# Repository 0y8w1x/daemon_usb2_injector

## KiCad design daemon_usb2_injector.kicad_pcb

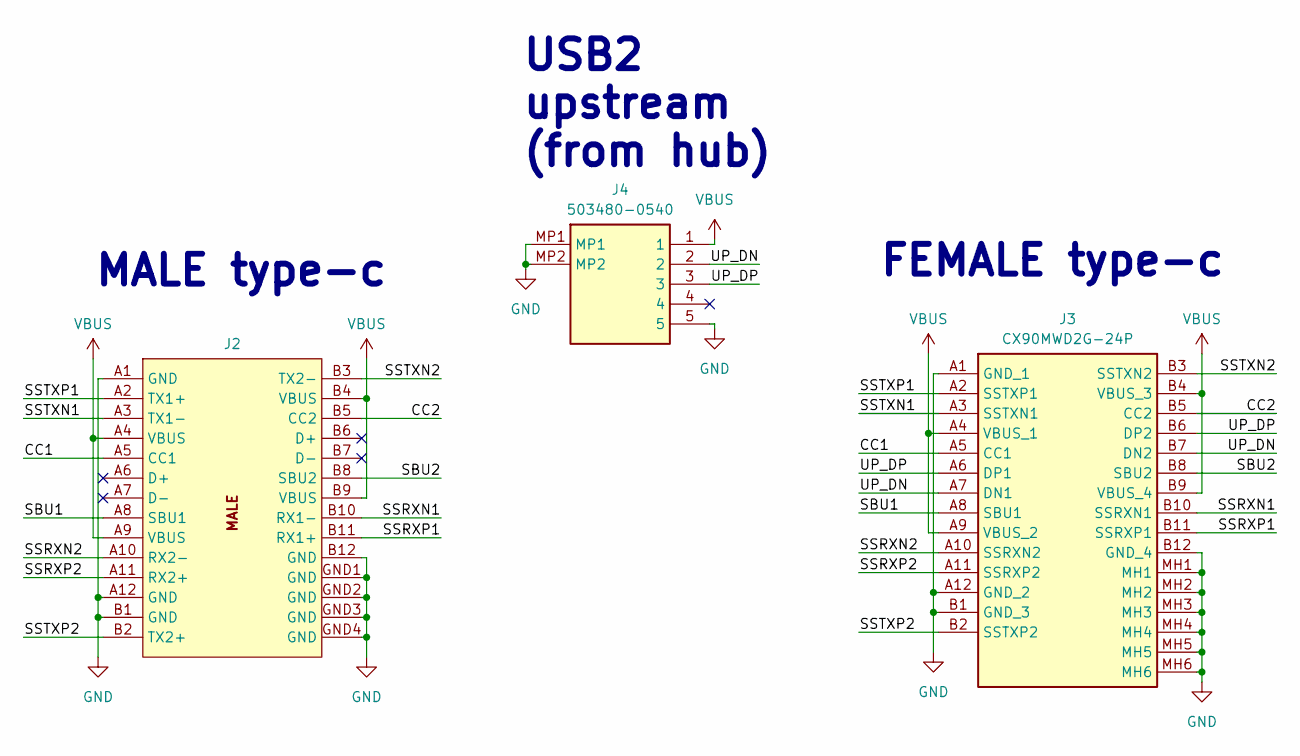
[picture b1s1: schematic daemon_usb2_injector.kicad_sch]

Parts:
J2: CX60-24S-UNIT
J3: CX90MWD2G-24P
J4: 503480-0540; 5034800540; Manufacturer_Part_Number 503480-0540; Mouser Part Number 538-503480-0540

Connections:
/CC1: J2.A5 (CC1), J3.A5 (CC1)
/CC2: J2.B5 (CC2), J3.B5 (CC2)
/SBU1: J2.A8 (SBU1), J3.A8 (SBU1)
/SBU2: J2.B8 (SBU2), J3.B8 (SBU2)
/SSRXN1: J2.B10 (RX1-), J3.B10 (SSRXN1)
/SSRXN2: J2.A10 (RX2-), J3.A10 (SSRXN2)
/SSRXP1: J2.B11 (RX1+), J3.B11 (SSRXP1)
/SSRXP2: J2.A11 (RX2+), J3.A11 (SSRXP2)
/SSTXN1: J2.A3 (TX1-), J3.A3 (SSTXN1)
/SSTXN2: J2.B3 (TX2-), J3.B3 (SSTXN2)
/SSTXP1: J2.A2 (TX1+), J3.A2 (SSTXP1)
/SSTXP2: J2.B2 (TX2+), J3.B2 (SSTXP2)
/UP_DN: J3.A7 (DN1), J3.B7 (DN2), J4.2
/UP_DP: J3.A6 (DP1), J3.B6 (DP2), J4.3
GND: J2.A1 (GND), J2.A12 (GND), J2.B1 (GND), J2.B12 (GND), J2.GND1 (GND), J2.GND2 (GND), J2.GND3 (GND), J2.GND4 (GND), J3.A1 (GND_1), J3.A12 (GND_2), J3.B1 (GND_3), J3.B12 (GND_4), J3.MH1, J3.MH2, J3.MH3, J3.MH4, J3.MH5, J3.MH6, J4.5, J4.MP1, J4.MP2
VBUS: J2.A4 (VBUS), J2.A9 (VBUS), J2.B4 (VBUS), J2.B9 (VBUS), J3.A4 (VBUS_1), J3.A9 (VBUS_2), J3.B4 (VBUS_3), J3.B9 (VBUS_4), J4.1

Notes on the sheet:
MALE type-c
USB2 upstream (from hub)
FEMALE type-c

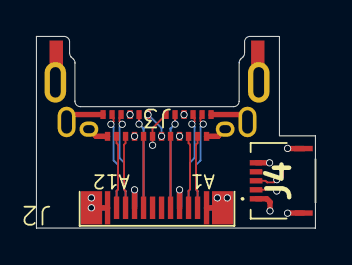
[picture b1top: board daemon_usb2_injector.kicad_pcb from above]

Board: 4 copper layers, 15.5 x 10.6 mm, 3 parts (0 on the bottom side), 16 nets.

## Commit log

2024-04-20 init
2024-07-27 changed files
